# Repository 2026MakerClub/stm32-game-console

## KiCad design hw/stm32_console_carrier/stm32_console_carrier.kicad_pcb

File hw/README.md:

# STM32 Arcade carrier PCB

A handheld-shaped carrier board for the course **mcudev STM32F4XX_Pro
(STM32F407ZGT6, "DevEBox")** and its 3.2" TFT. The DEB (with the TFT still
plugged into its New‑TFT header) pushes into two female headers on the
**back** of the carrier, and the TFT shows through a window. Pull it straight
out and the DEB is a plain dev board again.

```
 front ─┬─ TFT glass (sticks ~3 mm out of the window)
        ├─ carrier PCB 1.6 mm   ← this board: buttons, stick, buzzer on the front
        │    └─ 2× 2x30 female header, 8.5 mm (soldered on the BACK)
        ├─ ~11 mm gap           (DEB male pin plastic 2.5 + socket 8.5)
 back  ─┴─ DEB, component side facing the carrier; optional M3×11 standoffs
```

Pin map is the one in `fw_console/PINMAP.md`, so **no firmware change is needed**:

| Function | DEB pin | Carrier part |
|---|---|---|
| UP / DOWN / LEFT / RIGHT | PE1 / PE2 / PE3 / PE4 (J1 pins 1, 4, 3, 6) | SW1–SW4 (D-pad) |
| Stick X / Y | PC0 / PC1 (J1 19, 22) | U1 pots, powered from **3V3** |
| Stick push | PC4 (J1 31) | U1 switch |
| A (confirm) | PC5 (J1 34), the firmware's "stick 2 push" | SW5 |
| BACK | PB8 (J2 2), parallel with the DEB's KEY1 | SW6 |
| Sound | PA6 / TIM3_CH1 (J1 29) | Q1 S8050 → BZ1 buzzer and/or J3 speaker |
| Power | 3V3 (J1 59/60), 5V (J2 59), GND (J1 55, J2 58/60) | — |

## Files

| Path | What |
|---|---|
| `stm32_console_carrier/stm32_console_carrier.kicad_pro` | Open this in KiCad 10 |
| `…/stm32_console_carrier_gerbers.zip` | Gerbers and drill files. Upload as-is to JLCPCB/PCBWay |
| `…/stm32_console_carrier_schematic.pdf` | Schematic |
| `…/bom.csv` | Bill of materials |
| `…/render_top.png`, `render_bottom.png` | 3D renders |
| `…/fit_1to1.pdf` | 1:1 print for a paper test-fit |
| `…/erc.rpt`, `drc.rpt` | KiCad's own checks |
| `gen/` | The generator. Edit `gen/design.py`, then rerun |

Regenerate everything (about 5 minutes, mostly the autorouter):

```
"C:\Program Files\KiCad\10.0\bin\python.exe" hw\gen\build.py
```

Current check status: **ERC 0 errors, 0 warnings. DRC: 0 errors, 0
unconnected pads, schematic and PCB in sync.** One warning remains: one
thermal spoke on R2's GND pad is starved on F.Cu, but the pad is fully
connected on B.Cu.

## Measure before ordering

These numbers came from photos and from the stm32-base.org board page. **The
TFT size is a placeholder.** All of them are at the top of `gen/design.py`.

| # | Measure | Parameter | Current value |
|---|---|---|---|
| 1 | TFT module **PCB** (not the glass): length × width | `TFT_PCB_W`, `TFT_PCB_H` | 92 × 57 mm (guess) |
| 2 | With the TFT plugged in: TFT PCB centre vs DEB centre | `TFT_DX`, `TFT_DY` | 0, 0 |
| 3 | Outer pin row of header 1 to outer pin row of header 2, centre to centre | `HDR_OUTER_FROM_EDGE` = (74 − this) / 2 | 71.12 mm |
| 4 | Do the two headers' columns line up? (If not, the offset) | `HDR2_COL_SHIFT` | 0 |
| 5 | DEB centre to pin 1's column | `HDR_COL1_FROM_CENTRE` | 36.83 (header centred) |
| 6 | M3 hole centres, inset from the DEB corners | `DEB_HOLE_INSET_X/Y` | 3.5 mm |
| 7 | RST button centre from the DEB's left (USB) and top (header 1) edges | `DEB_RST_U/V` | 99.1, 7.9 mm |
| 8 | DEB top surface to TFT PCB underside (≈ carrier height) | (check only) | ~11 mm |

**The TFT must fit between the two header rows**, i.e. less than about 62 mm
across. If yours is wider, the carrier can't sit there. Tell me and the
mechanical concept changes.

Also check before soldering:

- **Joystick (U1):** the footprint is SparkFun's PS2 thumbstick pattern. Pots
  are on a 2.54 mm pitch, 10.16 mm from the centre, and the mounting tabs are at
  ±7.62 / ±6.67 mm. Lay your bare stick on a 1:1 print (see below) first.
- **Buzzer (BZ1):** pin 2 is a slot, so both 6.5 mm and 7.6 mm pitches fit.
  Use a **passive** buzzer, so melodies work.
- **Q1:** S8050 pinout is **E‑B‑C** with the flat side facing you. 2N2222A
  is **E‑B‑C** too in TO‑92, but check your batch.

**Cheapest sanity check:** print `stm32_console_carrier/fit_1to1.pdf` at **100 %**
(A4 landscape). Poke the DEB's pins through the paper and lay the TFT and the bare
stick on it, then confirm both header rows, the window and the stick pads line up.

## Assembly notes

1. Solder the **two 2x30 female headers on the BACK** (the side with the
   white DEB outline). Plug them onto the DEB first and solder with the DEB
   in place, so they come out perfectly aligned. Then unplug the DEB.
2. Front side: Q1, R1–R4, D1 (band = cathode = pin 1), C1 (+ marked), C2,
   buzzer (+ marked), switches, joystick.
3. **Trim all leads flush on the back of the left (D-pad) area.** The DEB's
   20‑pin JTAG/IDC plug and mini‑USB plugs come in underneath it. The IDC
   plug leaves only ~1.5 mm under the carrier.
4. Optional speaker: wire an 8 Ω 0.5 W speaker to J3 (`+` marked on the back)
   and glue it to the back, right side. Buzzer and speaker can both be fitted.
5. Optional: four M3 × 11 mm standoffs between the DEB's corner holes and
   H1–H4.

Bring-up: same stages as `fw_console/PINMAP.md` §5. The **I/O TEST** screen
shows every button, both stick axes and the sound. If a stick axis is
reversed, flip `JOY_INVERT_X/Y` in `fw_console/App/input.c`.

Things the carrier covers on the DEB: its RST button (poke it through the
notch at the window's top-right corner), K0/K1/WK_UP (BACK replaces K1), the
LEDs, the micro‑SD slot and the RTC battery.

## Ordering

2 layers, 1.6 mm FR‑4, 210 × 96 mm, min track/space 0.25/0.2 mm, min drill
0.3 mm, HASL. The TFT window is a normal routed internal cutout, so no
special option is needed. JLCPCB will price it as a >100 mm board.

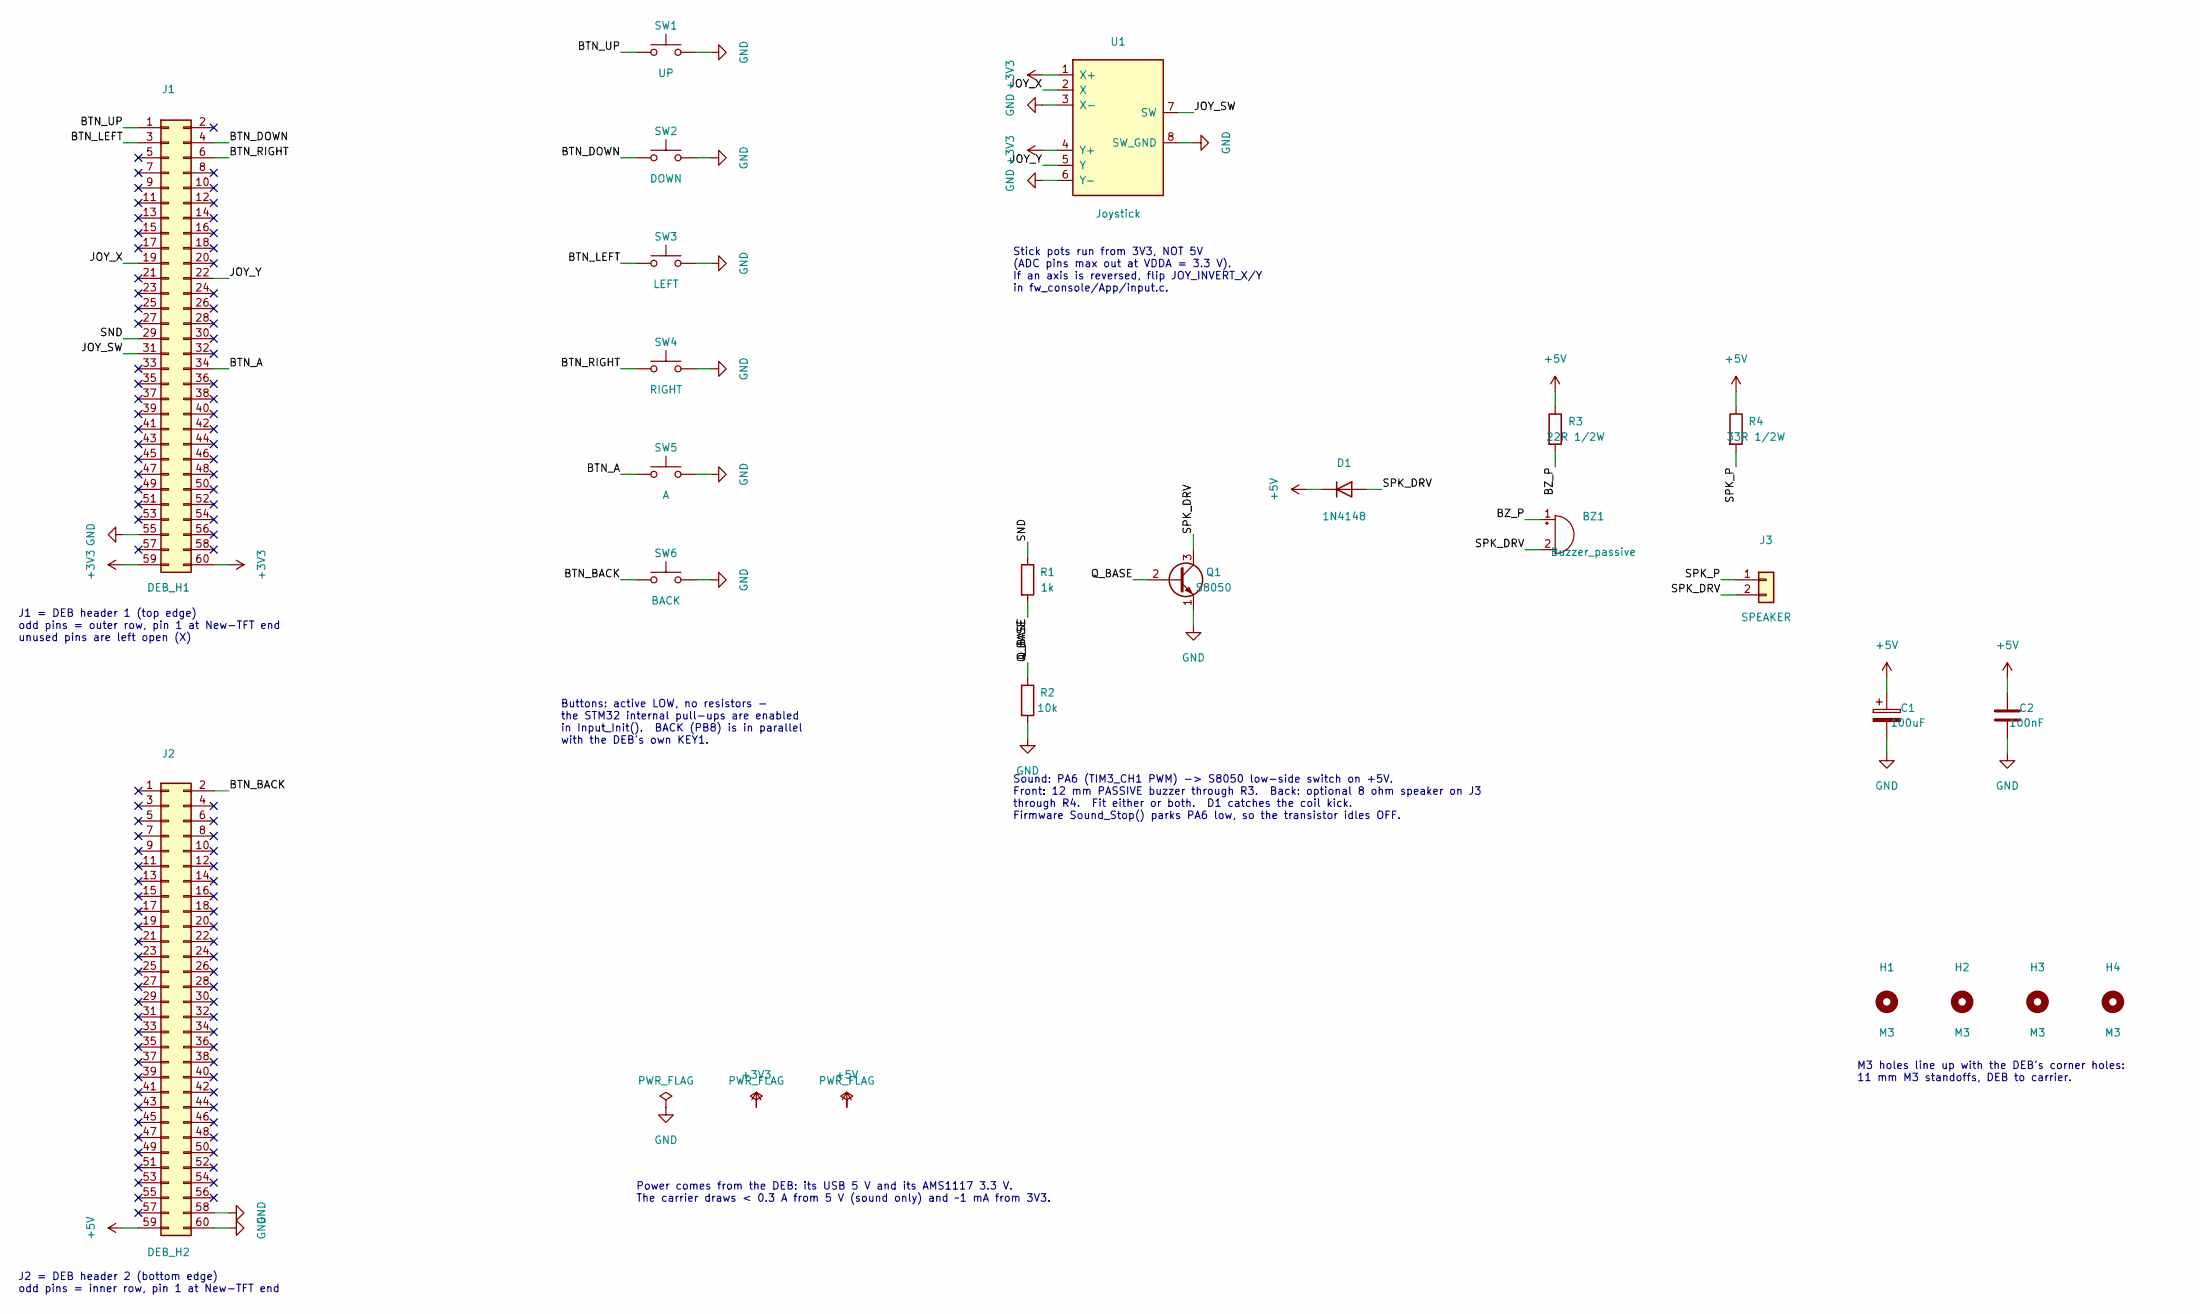
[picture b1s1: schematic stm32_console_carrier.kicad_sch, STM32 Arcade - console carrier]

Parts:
BZ1: Buzzer_passive; Buzzer_12mm_P6.5-7.6mm
C1: 100uF; CP_Radial_D6.3mm_P2.50mm
C2: 100nF; C_Disc_D5.0mm_W2.5mm_P2.50mm
D1: 1N4148; D_DO-35_SOD27_P2.54mm_Vertical_AnodeUp
H1, H2, H3, H4: M3; MountingHole_3.2mm_M3
J1: DEB_H1; PinSocket_2x30_P2.54mm_DEB
J2: DEB_H2; PinSocket_2x30_P2.54mm_DEB
J3: SPEAKER; PinHeader_1x02_P2.54mm_Vertical
Q1: S8050; TO-92_Inline
R1: 1k; R_Axial_DIN0207_L6.3mm_D2.5mm_P2.54mm_Vertical
R2: 10k; R_Axial_DIN0207_L6.3mm_D2.5mm_P2.54mm_Vertical
R3: 22R 1/2W; R_Axial_DIN0309_L9.0mm_D3.2mm_P2.54mm_Vertical
R4: 33R 1/2W; R_Axial_DIN0309_L9.0mm_D3.2mm_P2.54mm_Vertical
SW1: UP; SW_PUSH-12mm_Wuerth-430476085716
SW2: DOWN; SW_PUSH-12mm_Wuerth-430476085716
SW3: LEFT; SW_PUSH-12mm_Wuerth-430476085716
SW4: RIGHT; SW_PUSH-12mm_Wuerth-430476085716
SW5: A; SW_PUSH-12mm_Wuerth-430476085716
SW6: BACK; SW_PUSH-12mm_Wuerth-430476085716
U1: Joystick; Joystick_PS2_Thumb

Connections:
+3V3: J1.59, J1.60, U1.1 (X+), U1.4 (Y+)
+5V: C1.1, C2.1, D1.1 (K), J2.59, R3.1, R4.1
/BTN_A: J1.34, SW5.1
/BTN_BACK: J2.2, SW6.1
/BTN_DOWN: J1.4, SW2.1
/BTN_LEFT: J1.3, SW3.1
/BTN_RIGHT: J1.6, SW4.1
/BTN_UP: J1.1, SW1.1
/BZ_P: BZ1.1 (+), R3.2
/JOY_SW: J1.31, U1.7 (SW)
/JOY_X: J1.19, U1.2 (X)
/JOY_Y: J1.22, U1.5 (Y)
/Q_BASE: Q1.2 (B), R1.2, R2.1
/SND: J1.29, R1.1
/SPK_DRV: BZ1.2 (-), D1.2 (A), J3.2, Q1.3 (C)
/SPK_P: J3.1, R4.2
GND: C1.2, C2.2, J1.55, J2.58, J2.60, Q1.1 (E), R2.2, SW1.2, SW2.2, SW3.2, SW4.2, SW5.2, SW6.2, U1.3 (X-), U1.6 (Y-), U1.8 (SW_GND)

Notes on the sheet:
J1 = DEB header 1 (top edge) odd pins = outer row, pin 1 at New-TFT end unused pins are left open (X)
J2 = DEB header 2 (bottom edge) odd pins = inner row, pin 1 at New-TFT end
Buttons: active LOW, no resistors - the STM32 internal pull-ups are enabled in Input_Init(). BACK (PB8) is in parallel with the DEB's own KEY1.
Stick pots run from 3V3, NOT 5V (ADC pins max out at VDDA = 3.3 V). If an axis is reversed, flip JOY_INVERT_X/Y in fw_console/App/input.c.
Sound: PA6 (TIM3_CH1 PWM) -> S8050 low-side switch on +5V. Front: 12 mm PASSIVE buzzer through R3. Back: optional 8 ohm speaker on J3 through R4. Fit either or both. D1 catches the coil kick. Firmware Sound_Stop() parks PA6 low, so the transistor idles OFF.
M3 holes line up with the DEB's corner holes: 11 mm M3 standoffs, DEB to carrier.
Power comes from the DEB: its USB 5 V and its AMS1117 3.3 V. The carrier draws < 0.3 A from 5 V (sound only) and ~1 mA from 3V3.

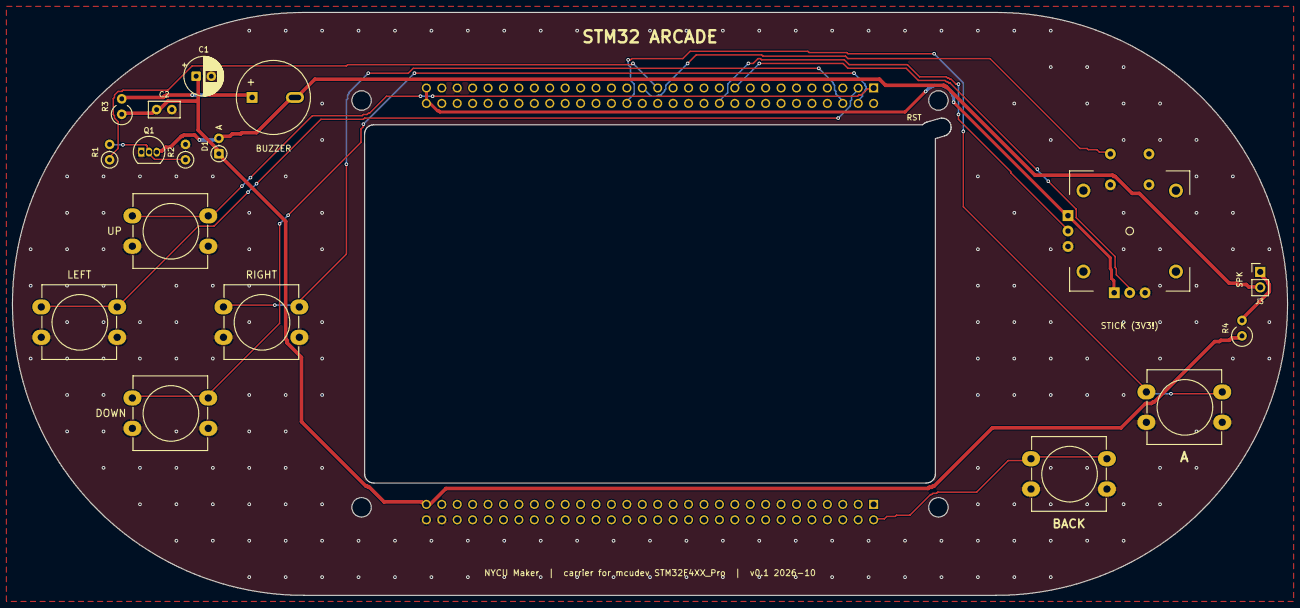
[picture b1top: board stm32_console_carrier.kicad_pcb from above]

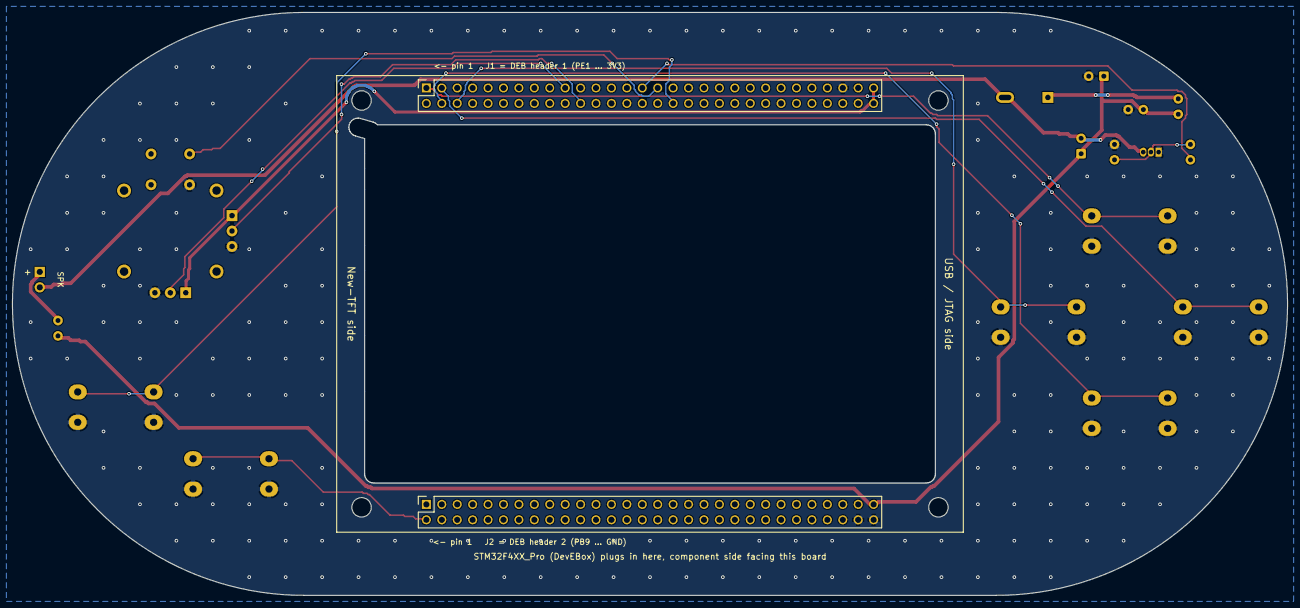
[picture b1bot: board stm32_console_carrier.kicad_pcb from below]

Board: 2 copper layers, 210.0 x 96.0 mm, 23 parts (2 on the bottom side), 17 nets.

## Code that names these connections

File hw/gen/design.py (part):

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JOY_X, JOY_Y = 79.0, -12.0

H1_NETS = {
    1: "BTN_UP",      # PE1
    3: "BTN_LEFT",    # PE3
    4: "BTN_DOWN",    # PE2
    6: "BTN_RIGHT",   # PE4
    19: "JOY_X",      # PC0  ADC1_IN10
    22: "JOY_Y",      # PC1  ADC1_IN11
    29: "SND",        # PA6  TIM3_CH1
    31: "JOY_SW",     # PC4
    34: "BTN_A",      # PC5  (stick-2 push input in firmware)
    55: "GND",
    59: "+3V3",
    60: "+3V3",
}
H2_NETS = {
    2: "BTN_BACK",    # PB8  (same as the DEB's KEY1)
    58: "GND",
    59: "+5V",
    60: "GND",
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SW12 = "Button_Switch_THT:SW_PUSH-12mm_Wuerth-430476085716"
SWDESC = "Tactile switch 12x12x7.3 mm THT + round cap"
part("SW1", "UP", "Switch:SW_Push", SW12, (DPAD_X, DPAD_Y - DPAD_S),
     pins={1: "BTN_UP", 2: "GND"}, desc=SWDESC)
part("SW2", "DOWN", "Switch:SW_Push", SW12, (DPAD_X, DPAD_Y + DPAD_S),
     pins={1: "BTN_DOWN", 2: "GND"}, desc=SWDESC)
part("SW3", "LEFT", "Switch:SW_Push", SW12, (DPAD_X - DPAD_S, DPAD_Y),
     pins={1: "BTN_LEFT", 2: "GND"}, desc=SWDESC)
part("SW4", "RIGHT", "Switch:SW_Push", SW12, (DPAD_X + DPAD_S, DPAD_Y),
     pins={1: "BTN_RIGHT", 2: "GND"}, desc=SWDESC)

# --- right thumb: stick + A / BACK -----------------------------------------
part("U1", "Joystick", "console:Joystick_2Axis_SW",
     "console:Joystick_PS2_Thumb", (JOY_X, JOY_Y),
     pins={1: "+3V3", 2: "JOY_X", 3: "GND",
           4: "+3V3", 5: "JOY_Y", 6: "GND",
           7: "JOY_SW", 8: "GND"},
     desc="PS2-style 2-axis thumb joystick, 10k pots + push switch "
          "(same part as on a KY-023 module)")
part("SW5", "A", "Switch:SW_Push", SW12, (88.0, 17.0),
     pins={1: "BTN_A", 2: "GND"}, desc=SWDESC)
part("SW6", "BACK", "Switch:SW_Push", SW12, (69.0, 28.0),
     pins={1: "BTN_BACK", 2: "GND"}, desc=SWDESC)

# --- sound: PA6 -> S8050 low-side switch -> buzzer (front) / speaker (back) -
part("BZ1", "Buzzer_passive", "Device:Buzzer",
     "console:Buzzer_12mm_P6.5-7.6mm", (-62.0, -34.0),
     pins={1: "BZ_P", 2: "SPK_DRV"},
     desc="12 mm PASSIVE magnetic buzzer, 3-5 V (pitch 6.5 or 7.6 mm both fit)")
part("Q1", "S8050", "Transistor_BJT:Q_NPN_EBC",
     "Package_TO_SOT_THT:TO-92_Inline", (-82.5, -25.0),
     pins={1: "GND", 2: "Q_BASE", 3: "SPK_DRV"},
     desc="S8050 NPN, TO-92, pinout E-B-C (2N2222A/SS8050 also fine if E-B-C)")
part("R1", "1k", "Device:R",
     "Resistor_THT:R_Axial_DIN0207_L6.3mm_D2.5mm_P2.54mm_Vertical", (-89.0, -25.0),
     rot=90, pins={1: "SND", 2: "Q_BASE"}, desc="Resistor 1 kOhm 1/4 W")
part("R2", "10k", "Device:R",
     "Resistor_THT:R_Axial_DIN0207_L6.3mm_D2.5mm_P2.54mm_Vertical", (-76.5, -25.0),
     rot=90, pins={1: "Q_BASE", 2: "GND"}, desc="Resistor 10 kOhm 1/4 W")
part("D1", "1N4148", "Device:D",
     "Diode_THT:D_DO-35_SOD27_P2.54mm_Vertical_AnodeUp", (-71.0, -26.0),
     rot=90, pins={1: "+5V", 2: "SPK_DRV"}, desc="1N4148 flyback diode")
part("R3", "22R 1/2W", "Device:R",
     "Resistor_THT:R_Axial_DIN0309_L9.0mm_D3.2mm_P2.54mm_Vertical", (-87.0, -32.5),
     rot=90, pins={1: "+5V", 2: "BZ_P"},
     desc="Resistor 22 Ohm 1/2 W (buzzer current limit)")
part("C1", "100uF", "Device:C_Polarized",
     "Capacitor_THT:CP_Radial_D6.3mm_P2.50mm", (-73.5, -37.5),
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     pins={1: "+5V", 2: "GND"}, desc="Ceramic 100 nF")
part("R4", "33R 1/2W", "Device:R",
     "Resistor_THT:R_Axial_DIN0309_L9.0mm_D3.2mm_P2.54mm_Vertical", (97.5, 4.0),
     rot=90, pins={1: "+5V", 2: "SPK_P"},
     desc="Resistor 33 Ohm 1/2 W (speaker current limit)")
part("J3", "SPEAKER", "Connector_Generic:Conn_01x02",
     "Connector_PinHeader_2.54mm:PinHeader_1x02_P2.54mm_Vertical", (100.5, -4.0),
     pins={1: "SPK_P", 2: "SPK_DRV"},
     desc="Speaker pads: solder an 8 Ohm 0.5 W speaker's wires here (optional)")

# --- mechanical -------------------------------------------------------------
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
